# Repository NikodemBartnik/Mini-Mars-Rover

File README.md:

Designed by [Nikodem Bartnik](https://www.youtube.com/nikodembartnik). 

Pico Mars Rover was built as an educational platform to inspire and let kids (but not only) learn about programming, electronics, tehnology and space. Build around the new Raspberry Pi Pico W can be programmed in MicroPython and controlled through WiFi with a server app written in Python. Of course all the electronics can be replaced with for example Arduino.
The chassis of the robot was built with [Open Robotic Platform](http://openroboticplatform.com) in mind so that it is easy to design holders, adapters and parts and reuse those you already have.
I used cheap and popular DC motors together with omniwheels but feel free to experiment and replace the parts according to your needs.

## Open Source
Project is open source and all the files and the code are available above. I would be more than happy if you would like to use it to teach and inspire others for example at robotics classes in your school! 

## Parts
The parts used for this project:
 - [Robot Chassis](https://amzn.to/3VZOzZ9)
 - [Raspberry Pi Pico](https://amzn.to/3ZqH3tj)
 - [Motors](https://amzn.to/3ka2aQf)
 - [Wheels](https://amzn.to/3GrcCKO)
 - [FPV camera](https://amzn.to/3IENinb)
 - [FPV screen](https://amzn.to/3CDmMqy)
 - [Battery](https://amzn.to/3GT1Rm2)
 - [Servos](https://amzn.to/3XpeDy7)

 If you buy the chassis like the one listed above you don't need to buy additional motors and wheels. All the parts are just examples. Use aht you have, what is more suitable for your project or what's currently cheaper.

## Arm
Have you seen a mars rover without a robotic arm? Exactly, that's why I also designed one for this project. It's all 3D printed and uses cheap microservo motors. The arm is not perfect and after some experiments I had to make all the links shorter which reduced the range of the arm but the small motors are very limited. Redesigning the arm for standard servo motors might be a good idea but it might be hard to fit it on the robot.

## FPV system
For trasmitting the video live fromt he robot I used a small FPV camera and a screen. It was the easiest to use and quite inexpensive solution that let you expierience controlling the robot from a "control room" at a distance based only on the camera view, sensors and the arm.

## Videos

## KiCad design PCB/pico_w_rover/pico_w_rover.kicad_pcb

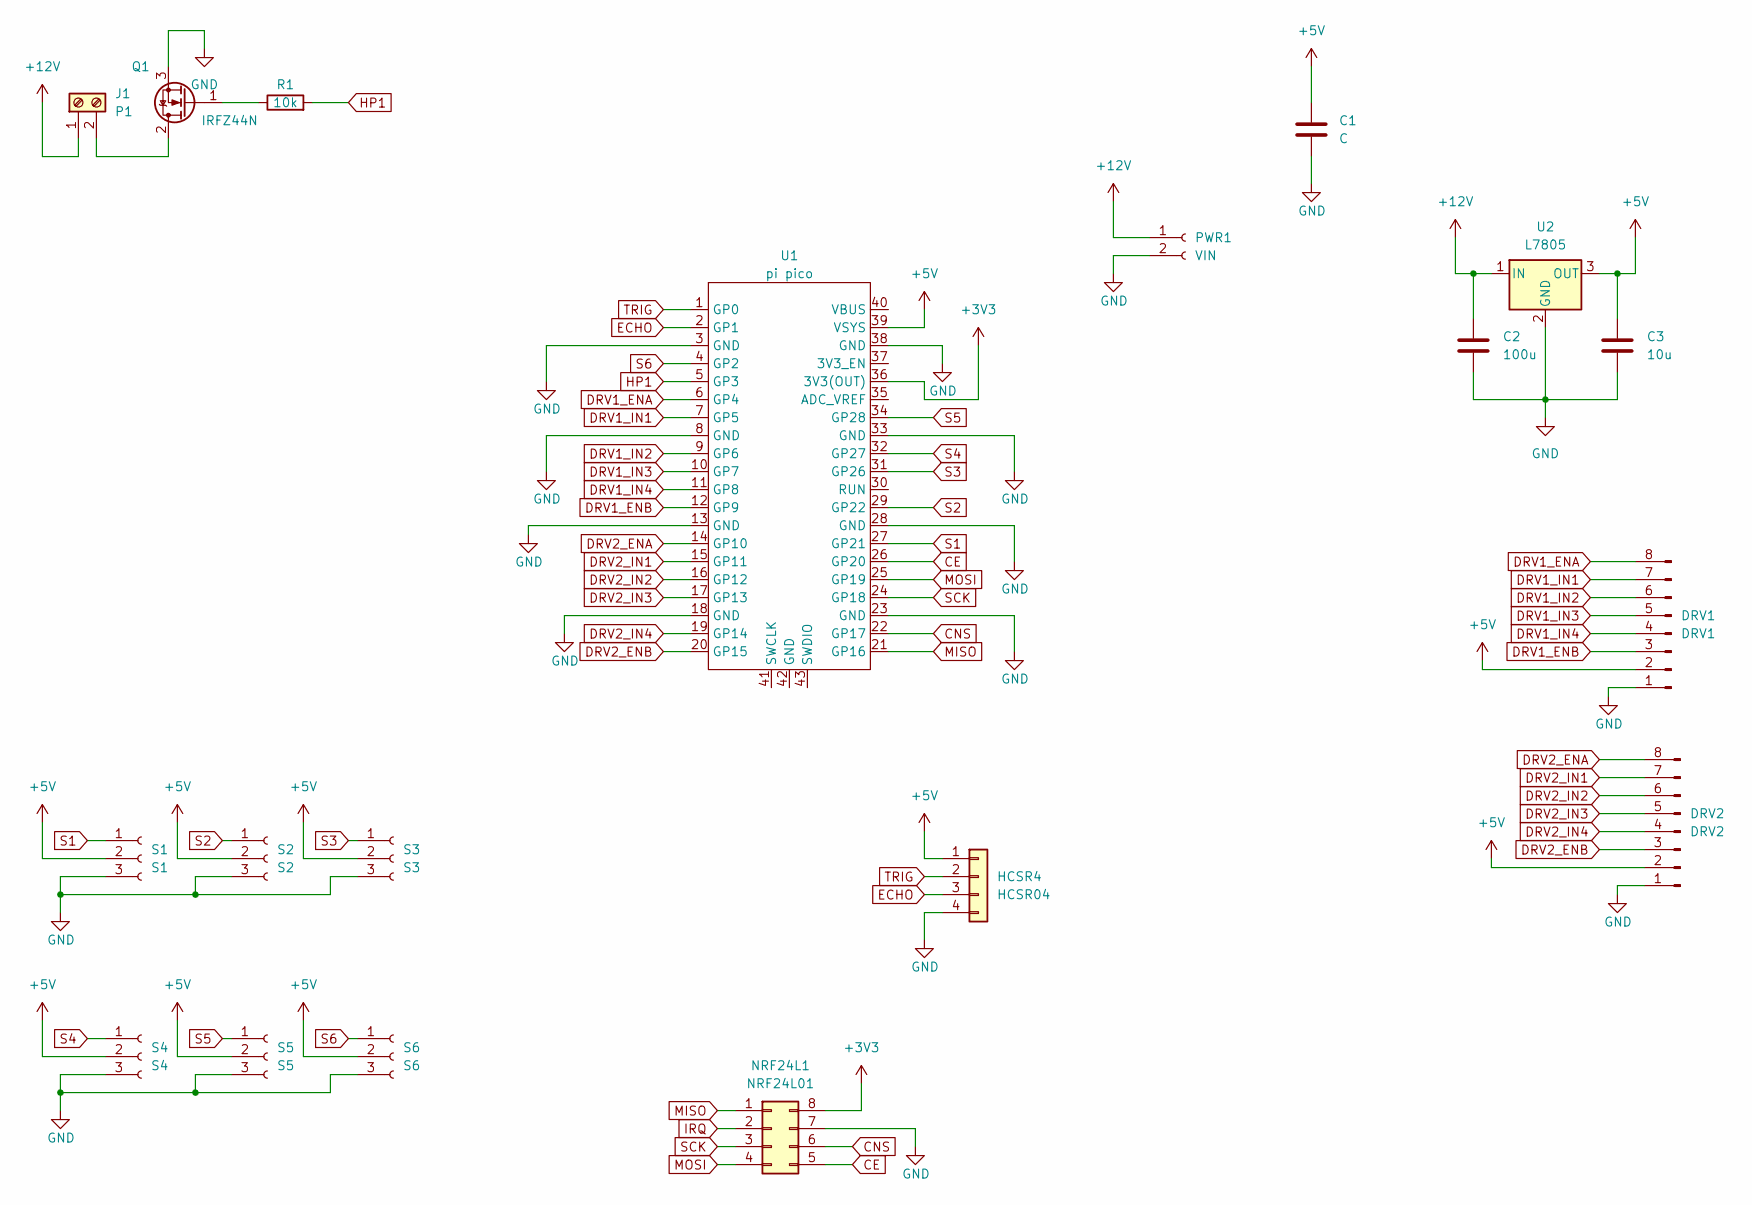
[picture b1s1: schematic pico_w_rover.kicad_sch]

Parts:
C1: C; C_Disc_D8.0mm_W5.0mm_P5.00mm
C2: 100u; C_Disc_D3.0mm_W2.0mm_P2.50mm
C3: 10u; C_Disc_D3.0mm_W2.0mm_P2.50mm
DRV1: DRV1; PinHeader_1x08_P2.54mm_Vertical
DRV2: DRV2; PinHeader_1x08_P2.54mm_Vertical
HCSR4: HCSR04; PinSocket_1x04_P2.54mm_Vertical
J1: P1; TerminalBlock_Phoenix_MKDS-1,5-2-5.08_1x02_P5.08mm_Horizont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
NRF24L1: NRF24L01; PinSocket_2x04_P2.54mm_Vertical
PWR1: VIN; PinHeader_1x02_P2.54mm_Vertical
Q1: IRFZ44N; TO-220-3_Vertical
R1: 10k; R_1206_3216Metric_Pad1.30x1.75mm_HandSolder
S1: S1; PinHeader_1x03_P2.54mm_Vertical
S2: S2; PinHeader_1x03_P2.54mm_Vertical
S3: S3; PinHeader_1x03_P2.54mm_Vertical
S4: S4; PinHeader_1x03_P2.54mm_Vertical
S5: S5; PinHeader_1x03_P2.54mm_Vertical
S6: S6; PinHeader_1x03_P2.54mm_Vertical
U1: pi pico; raspberry pi pico
U2: L7805; TO-220-3_Vertical

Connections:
+3V3: NRF24L1.8, U1.36 (3V3(OUT))
+5V: C1.1, C3.1, DRV1.2, DRV2.2, HCSR4.1, S1.2, S2.2, S3.2, S4.2, S5.2, S6.2, U1.39 (VSYS), U2.3 (OUT)
+12V: C2.1, J1.1, PWR1.1, U2.1 (IN)
CE: NRF24L1.5, U1.26 (GP20)
CNS: NRF24L1.6, U1.22 (GP17)
DRV1_ENA: DRV1.8, U1.6 (GP4)
DRV1_ENB: DRV1.3, U1.12 (GP9)
DRV1_IN1: DRV1.7, U1.7 (GP5)
DRV1_IN2: DRV1.6, U1.9 (GP6)
DRV1_IN3: DRV1.5, U1.10 (GP7)
DRV1_IN4: DRV1.4, U1.11 (GP8)
DRV2_ENA: DRV2.8, U1.14 (GP10)
DRV2_ENB: DRV2.3, U1.20 (GP15)
DRV2_IN1: DRV2.7, U1.15 (GP11)
DRV2_IN2: DRV2.6, U1.16 (GP12)
DRV2_IN3: DRV2.5, U1.17 (GP13)
DRV2_IN4: DRV2.4, U1.19 (GP14)
ECHO: HCSR4.3, U1.2 (GP1)
GND: C1.2, C2.2, C3.2, DRV1.1, DRV2.1, HCSR4.4, NRF24L1.7, PWR1.2, Q1.3 (S), S1.3, S2.3, S3.3, S4.3, S5.3, S6.3, U1.3 (GND), U1.8 (GND), U1.13 (GND), U1.18 (GND), U1.23 (GND), U1.28 (GND), U1.33 (GND), U1.38 (GND), U2.2 (GND)
HP1: R1.2, U1.5 (GP3)
IRQ: NRF24L1.2
MISO: NRF24L1.1, U1.21 (GP16)
MOSI: NRF24L1.4, U1.25 (GP19)
unnamed: J1.2, Q1.2 (D)
unnamed: Q1.1 (G), R1.1
S1: S1.1, U1.27 (GP21)
S2: S2.1, U1.29 (GP22)
S3: S3.1, U1.31 (GP26)
S4: S4.1, U1.32 (GP27)
S5: S5.1, U1.34 (GP28)
S6: S6.1, U1.4 (GP2)
SCK: NRF24L1.3, U1.24 (GP18)
TRIG: HCSR4.2, U1.1 (GP0)

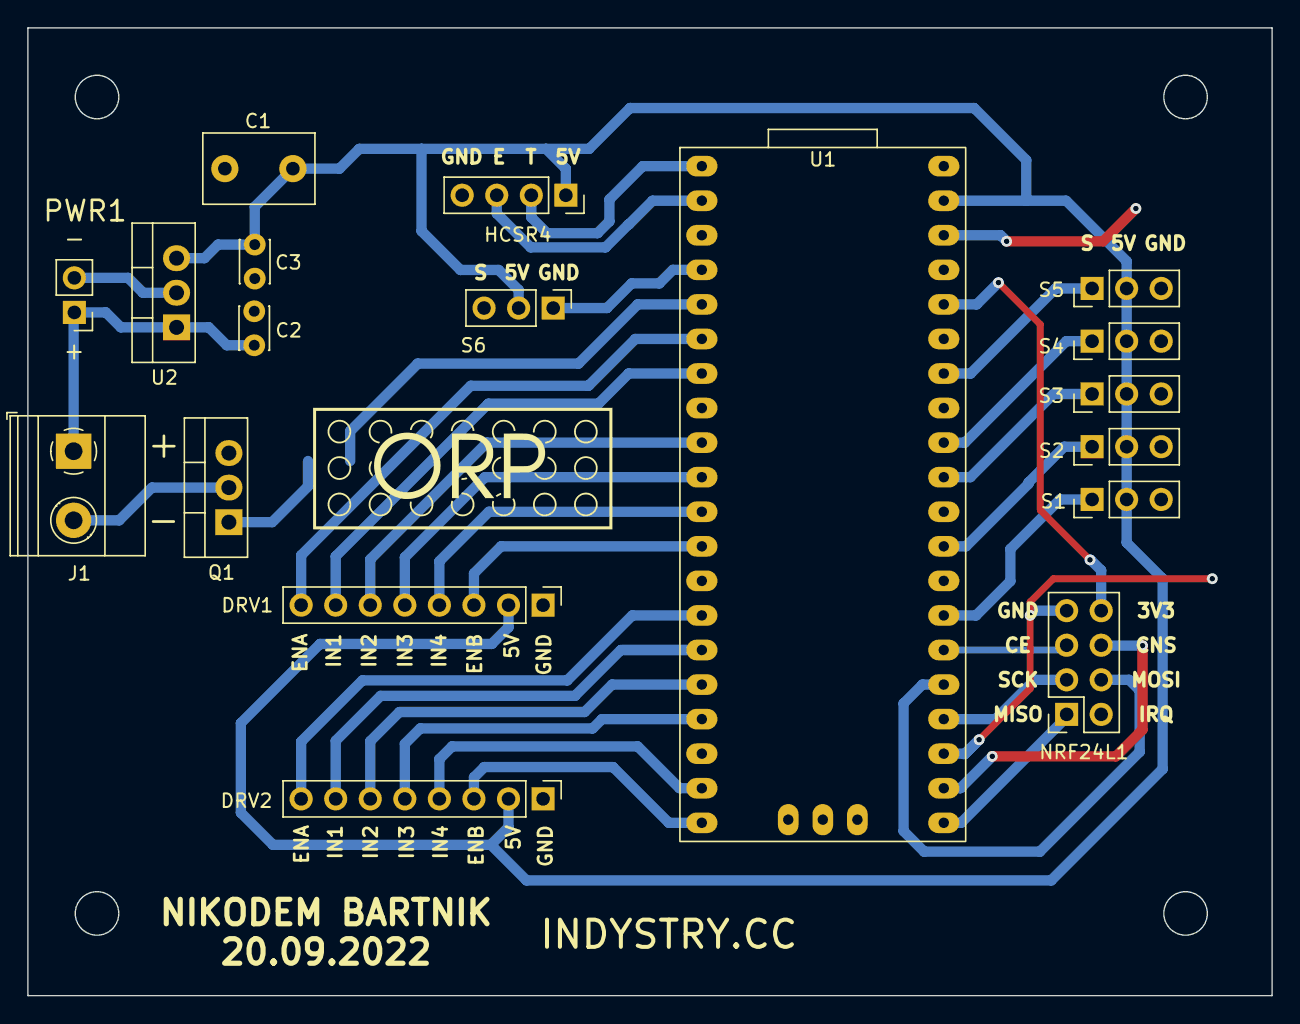
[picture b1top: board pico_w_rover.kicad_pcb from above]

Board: 2 copper layers, 91.4 x 71.1 mm, 19 parts (1 on the bottom side), 32 nets.

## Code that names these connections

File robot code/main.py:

import network, socket, time
from machine import Pin, PWM

SERVO_CALIBRATION_VALUE = 0.60


led = Pin("LED", Pin.OUT)
camera_pin = Pin(3, Pin.OUT)
drv1_in1 = Pin(5, Pin.OUT)
drv1_in2 = Pin(6, Pin.OUT)
drv1_in3 = Pin(7, Pin.OUT)
drv1_in4 = Pin(8, Pin.OUT)
drv2_in1 = Pin(11, Pin.OUT)
drv2_in2 = Pin(12, Pin.OUT)
drv2_in3 = Pin(13, Pin.OUT)
drv2_in4 = Pin(14, Pin.OUT)

camera_pin.value(0)


servo1 = PWM(Pin(21))
servo2 = PWM(Pin(22))
servo3 = PWM(Pin(26))
servo4 = PWM(Pin(27))
drv1_a = PWM(Pin(4))
drv1_b = PWM(Pin(9))
drv2_a = PWM(Pin(10))
drv2_b = PWM(Pin(15))


servo1.freq(50)
servo2.freq(50)
servo3.freq(50)
servo4.freq(50)
drv1_a.freq(50)
drv1_b.freq(50)
drv2_a.freq(50)
drv2_b.freq(50)

wlan = network.WLAN(network.STA_IF)
wlan.active(True)
wlan.connect('TP-LINK_B71D9D', '87057850')
soc = socket.socket()
# Should be connected and have an IP address
#wlan.status() # 3 == success
#wlan.ifconfig()
time.sleep(5)
    
def servoSet(servo, duty):
    servo.duty_u16(int((1-SERVO_CALIBRATION_VALUE)*3277 + (duty/180) * 3277*(SERVO_CALIBRATION_VALUE+1)))
    
#duty form 0 to 1
#M1 front right, 1 - backwards, 0 - forward
#M2 back right, 1- backwards, 0 - forward
#M3 front left, 1- backwards, 0 - forward
#M4 back left, 1- backwards, 0 - forward
def setMotor(motor, dir, duty):
    if motor is 1:
        drv1_in1.value(dir)
        drv1_in2.value(not dir)
        drv1_a.duty_u16(int(65536 * duty))
    elif motor is 2:
        drv1_in3.value(dir)
        drv1_in4.value(not dir)
        drv1_b.duty_u16(int(65536 * duty))
    elif motor is 3:
        drv2_in1.value(not dir)
        drv2_in2.value(dir)
        drv2_a.duty_u16(int(65536 * duty))
    elif motor is 4:
        drv2_in3.value(not dir)
        drv2_in4.value(dir)
        drv2_b.duty_u16(int(65536 * duty))
    
def drive(value, power):
    print(power)
    if value < 120 and value > 60:
        setMotor(1, 0, power)
        setMotor(2, 0, power)
        setMotor(3, 0, power)
        setMotor(4, 0, power)
    elif value < 210 and value > 150:
        setMotor(1, 0, power)
        setMotor(2, 1, power)
        setMotor(3, 1, power)
        setMotor(4, 0, power)
    elif value > 330 or value < 30:
        setMotor(1, 1, power)
        setMotor(2, 0, power)
        setMotor(3, 0, power)
        setMotor(4, 1, power)
    elif value < 300 and value > 240:
        setMotor(1, 1, power)
        setMotor(2, 1, power)
        setMotor(3, 1, power)
        setMotor(4, 1, power)
        
        
def turn(direction):
    if direction:
        setMotor(1, 0, 0.7)
        setMotor(2, 0, 0.7)
        setMotor(3, 1, 0.7)
        setMotor(4, 1, 0.7)
    else:
        setMotor(1, 1, 0.7)
        setMotor(2, 1, 0.7)
        setMotor(3, 0, 0.7)
        setMotor(4, 0, 0.7)
    
def stop():
    drv1_a.duty_u16(0)
    drv1_b.duty_u16(0)
    drv2_a.duty_u16(0)
    drv2_b.duty_u16(0)
    

soc.connect(("192.168.1.107", 12345))

while True:
    data = soc.readline()
    values = str(data,'utf8').strip().split(',')
    values = [int(x) for x in values]
    print(values, end='\n')
    servoSet(servo1, values[0]/10)
    servoSet(servo2, values[1]/10)
    servoSet(servo3, values[2]/10)
    servoSet(servo4, values[3]/10)
    
    
    if values[4] is -10:
        stop()
    else:
        drive(int(values[4]/10), values[5]/100)
        
    if values[7] is 1:
        turn(1)
    elif values[7] is 2:
        turn(0)
        
    
    if values[6] is 1:
        camera_pin.value(1)
        led.value(1)
    else:
        camera_pin.value(0)
        led.value(0)

    
    #s.send('hello')

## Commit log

2022-10-18 readme update
2022-10-18 thumbnail added
2022-12-23 added base plate file #1
2023-01-10 fixed links
